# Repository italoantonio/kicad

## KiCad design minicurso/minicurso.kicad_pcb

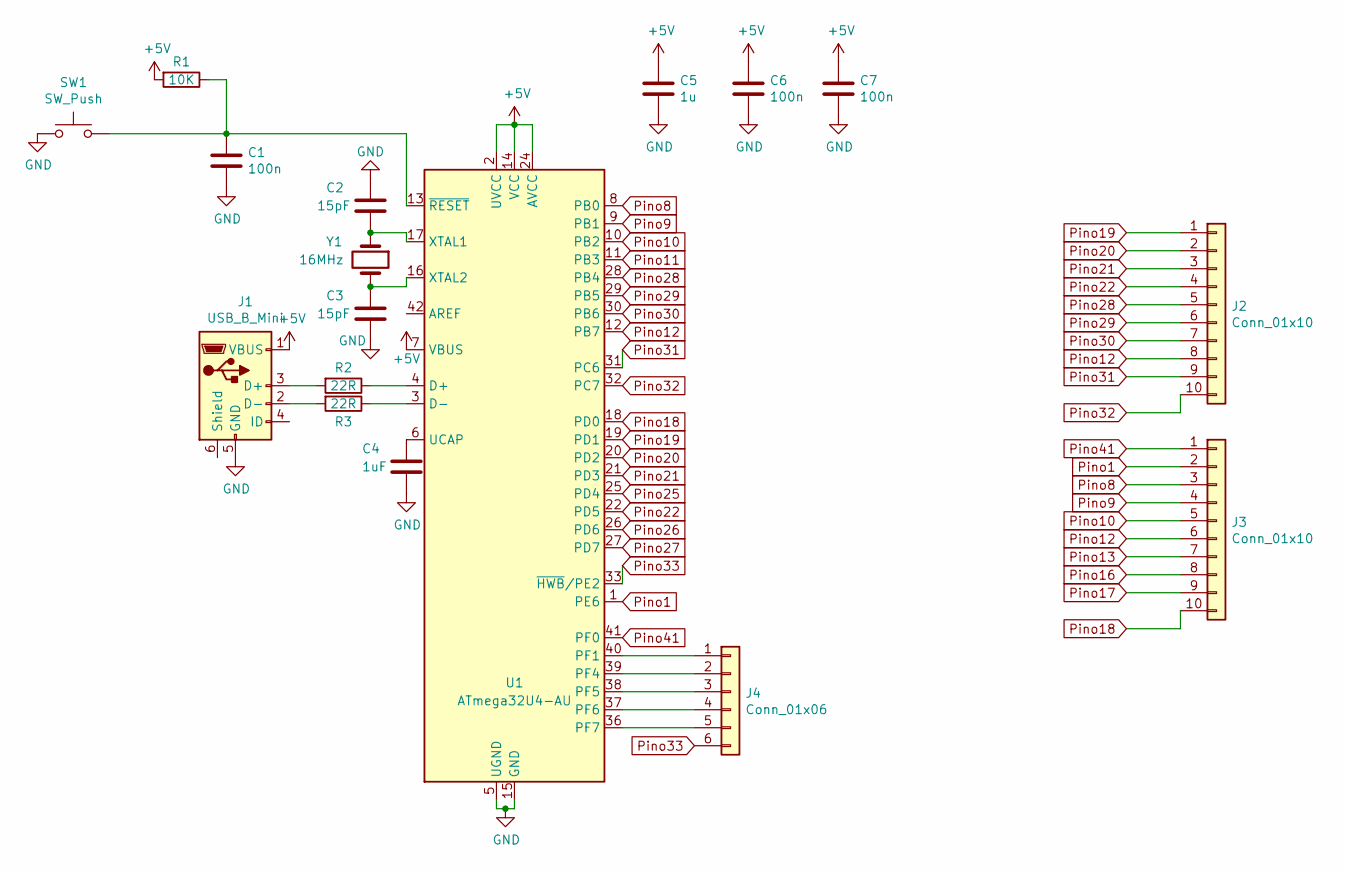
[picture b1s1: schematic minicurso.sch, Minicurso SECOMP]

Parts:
C1, C6, C7: 100n; C_0805_2012Metric_Pad1.15x1.40mm_HandSolder
C2, C3: 15pF; C_0805_2012Metric_Pad1.15x1.40mm_HandSolder
C4: 1uF; C_0805_2012Metric_Pad1.15x1.40mm_HandSolder
C5: 1u; C_0805_2012Metric_Pad1.15x1.40mm_HandSolder
J1: USB_B_Mini; USB_Mini-B_AdamTech_MUSB-B5-S-VT-TSMT-1_SMD_Vertical
J2, J3: Conn_01x10; PinHeader_1x10_P2.54mm_Vertical
J4: Conn_01x06; PinHeader_1x06_P2.54mm_Vertical
R1: 10K; R_1206_3216Metric_Pad1.42x1.75mm_HandSolder
R2, R3: 22R; R_1206_3216Metric_Pad1.42x1.75mm_HandSolder
SW1: SW_Push; SW_PUSH_6mm
U1: ATmega32U4-AU; TQFP-44_10x10mm_P0.8mm
Y1: 16MHz; Crystal_SMD_5032-2Pin_5.0x3.2mm_HandSoldering

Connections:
+5V: C5.1, C6.1, C7.1, J1.1 (VBUS), R1.2, U1.2 (UVCC), U1.7 (VBUS), U1.14 (VCC), U1.24 (AVCC), U1.34 (VCC), U1.44 (AVCC)
GND: C1.2, C2.1, C3.2, C4.2, C5.2, C6.2, C7.2, J1.5 (GND), SW1.1, U1.5 (UGND), U1.15 (GND), U1.23 (GND), U1.35 (GND), U1.43 (GND)
unnamed: C1.1, R1.1, SW1.2, U1.13 (~RESET)
unnamed: C2.2, U1.17 (XTAL1), Y1.1
unnamed: C3.1, U1.16 (XTAL2), Y1.2
unnamed: C4.1, U1.6 (UCAP)
unnamed: J1.2 (D-), R3.2
unnamed: J1.3 (D+), R2.2
unnamed: J4.1, U1.40 (PF1)
unnamed: J4.2, U1.39 (PF4)
unnamed: J4.3, U1.38 (PF5)
unnamed: J4.4, U1.37 (PF6)
unnamed: J4.5, U1.36 (PF7)
unnamed: R2.1, U1.4 (D+)
unnamed: R3.1, U1.3 (D-)
Pino1: J3.2, U1.1 (PE6)
Pino8: J3.3, U1.8 (PB0)
Pino9: J3.4, U1.9 (PB1)
Pino10: J3.5, U1.10 (PB2)
Pino11: U1.11 (PB3)
Pino12: J2.8, J3.6, U1.12 (PB7)
Pino13: J3.7
Pino16: J3.8
Pino17: J3.9
Pino18: J3.10, U1.18 (PD0)
Pino19: J2.1, U1.19 (PD1)
Pino20: J2.2, U1.20 (PD2)
Pino21: J2.3, U1.21 (PD3)
Pino22: J2.4, U1.22 (PD5)
Pino25: U1.25 (PD4)
Pino26: U1.26 (PD6)
Pino27: U1.27 (PD7)
Pino28: J2.5, U1.28 (PB4)
Pino29: J2.6, U1.29 (PB5)
Pino30: J2.7, U1.30 (PB6)
Pino31: J2.9, U1.31 (PC6)
Pino32: J2.10, U1.32 (PC7)
Pino33: J4.6, U1.33 (~HWB~/PE2)
Pino41: J3.1, U1.41 (PF0)

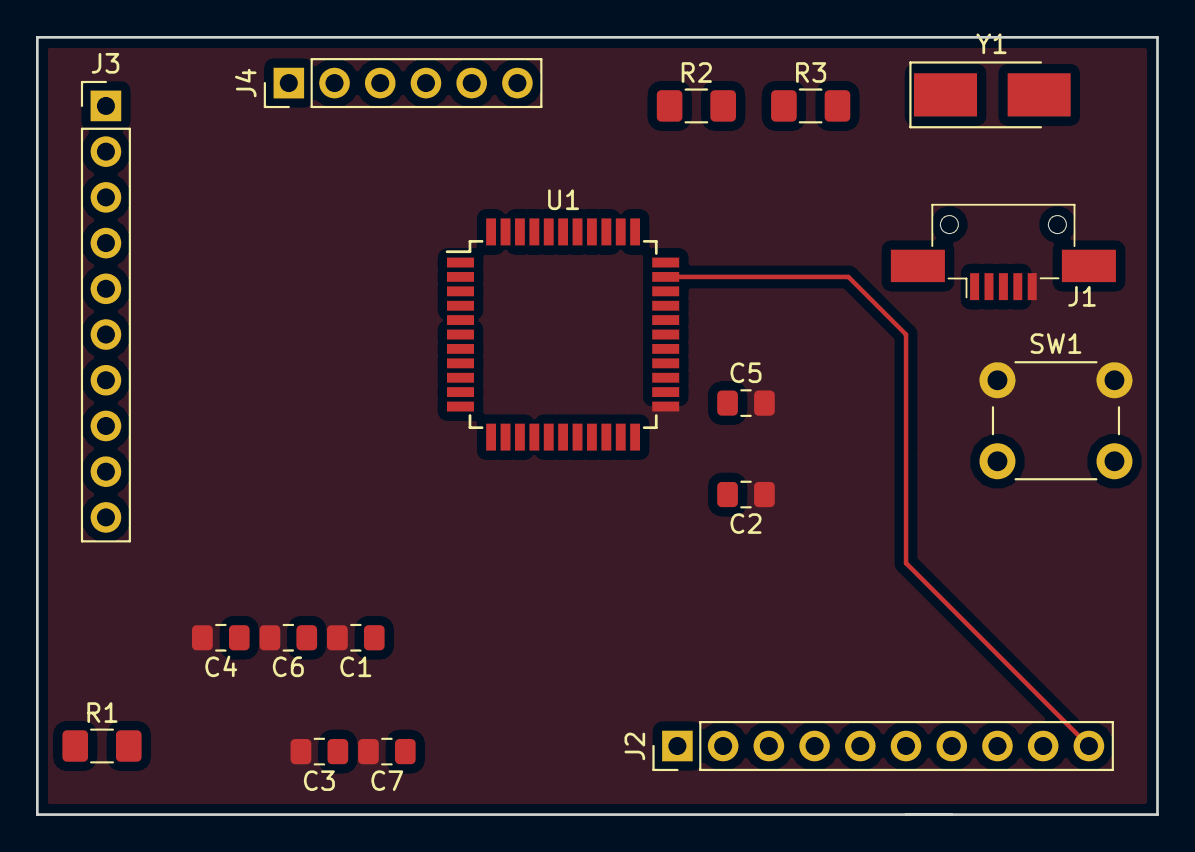
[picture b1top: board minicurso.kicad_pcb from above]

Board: 2 copper layers, 62.2 x 43.2 mm, 17 parts (0 on the bottom side), 32 nets.

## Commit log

2019-09-12 Test
2019-09-12 MSU e USB adicionados
2019-09-12 Add crystal, ucamp and bypass
2019-09-12 Add reset and pinheaders
2019-09-12 Adicionar anotacoes
2019-09-12 Adicionada as foodprints
2019-09-12 Dsenho e plot3d
2019-09-12 Usando label para facilitar desenho
2019-09-12 Gerbers files
